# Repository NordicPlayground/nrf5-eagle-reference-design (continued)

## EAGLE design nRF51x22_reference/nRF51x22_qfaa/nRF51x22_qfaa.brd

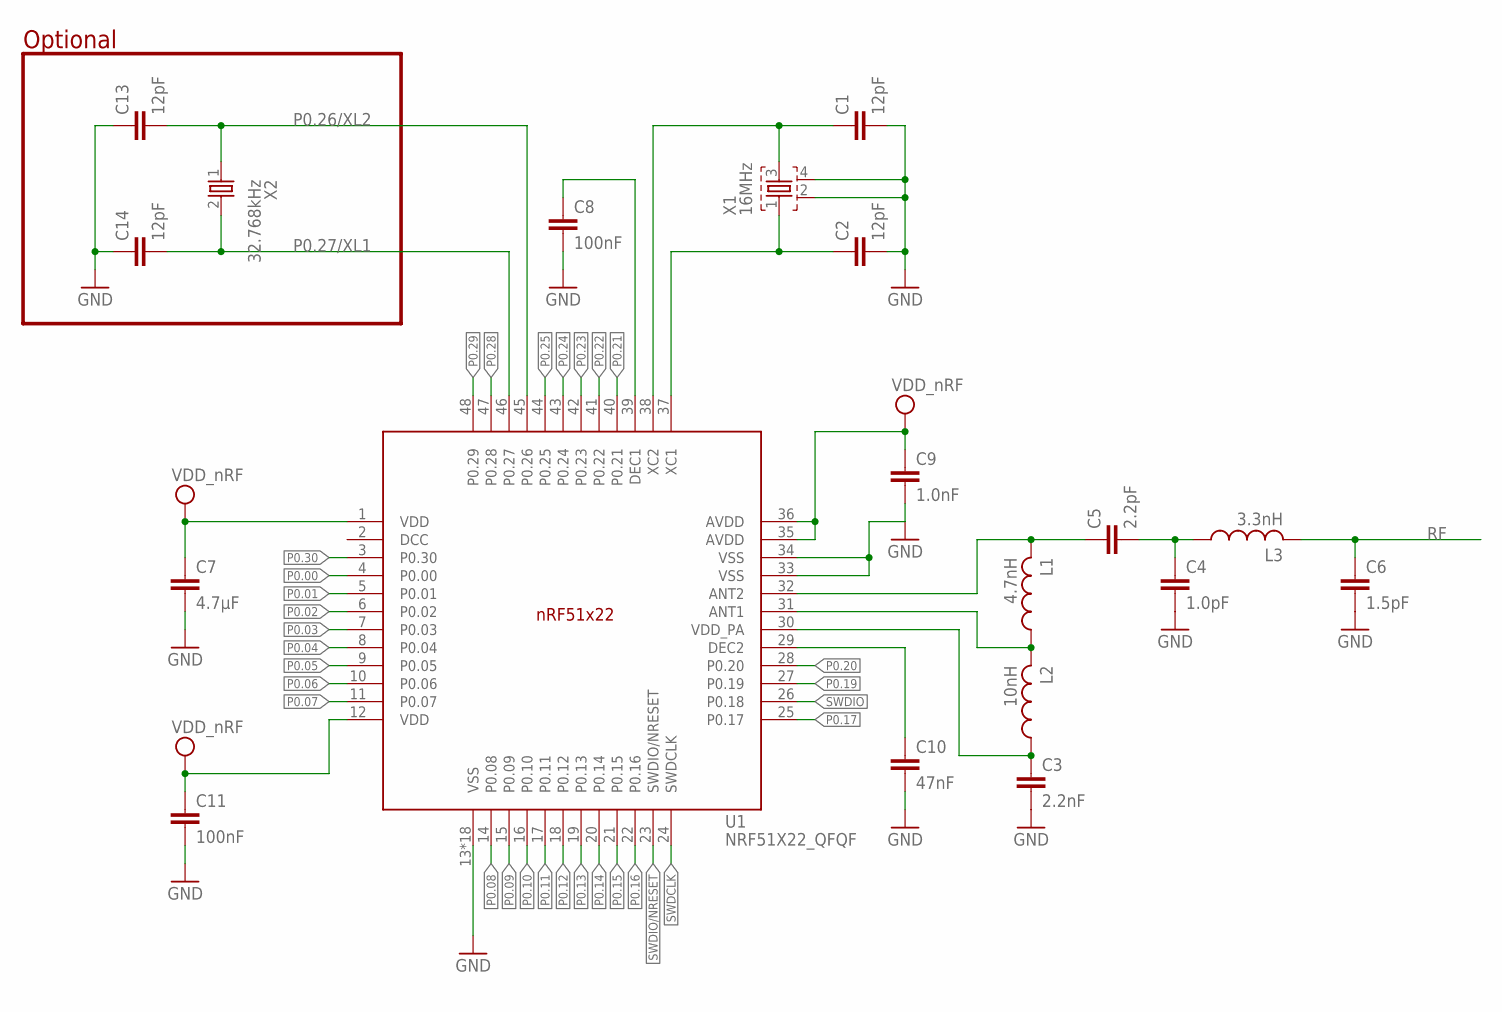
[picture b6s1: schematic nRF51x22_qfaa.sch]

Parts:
C1, C2, C13, C14: 12pF; RESC0402_N
C3: 2.2nF; RESC0402_N
C4: 1.0pF; RESC0402_N
C5: 2.2pF; RESC0402_N
C6: 1.5pF; RESC0402_N
C7: 4.7µF; RESC0603_N
C8, C11: 100nF; RESC0402_N
C9: 1.0nF; RESC0402_N
C10: 47nF; RESC0402_N
L1: 4.7nH; RESC0402_N
L2: 10nH; RESC0402_N
L3: 3.3nH; RESC0402_N
U1: NRF51X22_QFQF; QFN40P600X600X90-48_N
X1: 16MHz; BT-XTAL_2016_N
X2: 32.768kHz; XTAL_3215_N

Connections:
DCC: U1.2 (DCC)
GND: C1.2, C2.2, C3.2, C4.2, C6.2, C7.2, C8.2, C9.2, C10.2, C11.2, C13.1, C14.1, U1.13 (VSS), U1.33 (VSS), U1.34 (VSS), U1.PAD (VSS), U1.PAD@VIA01 (VSS), U1.PAD@VIA02 (VSS), U1.PAD@VIA03 (VSS), U1.PAD@VIA04 (VSS), U1.PAD@VIA05 (VSS), U1.PAD@VIA06 (VSS), U1.PAD@VIA07 (VSS), U1.PAD@VIA08 (VSS), U1.PAD@VIA09 (VSS), U1.PAD@VIA10 (VSS), U1.PAD@VIA11 (VSS), U1.PAD@VIA12 (VSS), U1.PAD@VIA13 (VSS), U1.PAD@VIA14 (VSS), U1.PAD@VIA15 (VSS), U1.PAD@VIA16 (VSS), X1.2, X1.4
unnamed: L1.1, L2.2, U1.31 (ANT1)
unnamed: C1.1, U1.38 (XC2), X1.3
unnamed: C10.1, U1.29 (DEC2)
unnamed: C8.1, U1.39 (DEC1)
unnamed: C3.1, L2.1, U1.30 (VDD_PA)
unnamed: C5.1, L1.2, U1.32 (ANT2)
unnamed: C4.1, C5.2, L3.1
P0.00: U1.4 (P0.00)
P0.01: U1.5 (P0.01)
P0.02: U1.6 (P0.02)
P0.03: U1.7 (P0.03)
P0.04: U1.8 (P0.04)
P0.05: U1.9 (P0.05)
P0.06: U1.10 (P0.06)
P0.07: U1.11 (P0.07)
P0.08: U1.14 (P0.08)
P0.09: U1.15 (P0.09)
P0.10: U1.16 (P0.10)
P0.11: U1.17 (P0.11)
P0.12: U1.18 (P0.12)
P0.13: U1.19 (P0.13)
P0.14: U1.20 (P0.14)
P0.15: U1.21 (P0.15)
P0.16: U1.22 (P0.16)
P0.17: U1.25 (P0.17)
P0.19: U1.27 (P0.19)
P0.20: U1.28 (P0.20)
P0.21: U1.40 (P0.21)
P0.22: U1.41 (P0.22)
P0.23: U1.42 (P0.23)
P0.24: U1.43 (P0.24)
P0.25: U1.44 (P0.25)
P0.26/XL2: C13.2, U1.45 (P0.26), X2.1
P0.27/XL1: C14.2, U1.46 (P0.27), X2.2
P0.28: U1.47 (P0.28)
P0.29: U1.48 (P0.29)
P0.30: U1.3 (P0.30)
RF: C6.1, L3.2
SWDCLK: U1.24 (SWDCLK)
SWDIO: U1.26 (P0.18)
SWDIO/NRESET: U1.23 (SWDIO/NRESET)
VDD_NRF: C7.1, C9.1, C11.1, U1.1 (VDD), U1.12 (VDD), U1.35 (AVDD), U1.36 (AVDD)
X1: C2.1, U1.37 (XC1), X1.1

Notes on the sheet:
Optional

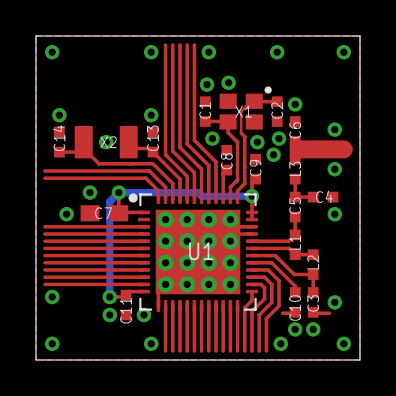
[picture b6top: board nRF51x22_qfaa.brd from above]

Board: 2 copper layers, 18.0 x 18.0 mm, 19 parts (0 on the bottom side), 13 nets.

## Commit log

2016-06-15 Finished? footprint and symbol for nRF5, QFN. Done som experimenting on board layouts
2016-06-15 Changd layer of silkscreen
2016-06-15 Fixed chip components(resistors) Moved physical outline to tDocu layer
2016-06-15 Added description on nRF chips
2016-06-16 Connected BGA package and symbols
2016-06-16 Added antennas, added passive components
2016-06-16 Fixed paste, and soldermask layers in antennas
2016-06-16 Fixed silkscreen on meander antenna
2016-06-17 Added SOT223 and TLV1117
2016-06-17 Added courtyard to XTAL2016
2016-06-17 Added courtyard to XTAL3215
2016-06-17 Renamed pads on XTAL3215 (removed $)
2016-06-17 Renamed pads on XTAL2016 (removed $)
2016-06-17 Moved resistor value inside resistor
2016-06-17 Added MM8130-2600
2016-06-17 Added NFC and SWO to symbol for nrf52
2016-06-20 Added microusb
2016-06-20 Routed gpio
2016-06-21 Added switches
2016-06-21 Positioned buttons, positioned powersupply
2016-06-21 Removed all non-library files (not ready for publishing)
2016-06-21 Split library into two, nRF (core parts), and misc
2016-06-21 Added brief readme
2016-06-21 punctuation
2016-06-21 Added licence (TBC?)
2016-06-21 Readded nRF52832_MCU_Board
2016-06-21 Fixed library links
2016-06-21 Added LED
2016-06-21 Fixed polarity on CR1632
2016-06-21 Done some layout
2016-06-21 Squezed in nfc antenna connector
2016-06-21 Connected all signals in layout
2016-06-21 Copyed layout from nano to arduino
2016-06-22 Copied altium reference designs
2016-06-22 Added more vias
2016-06-22 Added NFC antenna
2016-06-22 Looked at arduino layout
2016-06-22 Started Getting-started.md
2016-06-23 Copied reference layout from altium
2016-06-23 Removed old files
2016-06-23 Cleanup in layout
2016-06-23 Added two connections to CR1632
2016-06-23 Added some vias
2016-06-23 Generated pdfs of reference designs
2016-06-23 Cleaned up schematic
2016-06-23 Written some more on getting started
2016-06-23 Looked into different layout
2016-06-27 Written more detailed
2016-06-28 Restructured MCU_Board
2016-06-28 Regenerated pdfs with polygons pured
2016-06-28 Rearranged
2016-06-28 png for getting started
2016-06-28 resized
2016-06-28 Removed dummy text
2016-06-28 Copy pasted from getting started to readme
2016-06-28 Fixed comments from David Garcia Polo
2016-06-30 Added silk, name and value to FPC_05P-RA-SMD
2016-06-30 Aded name and value to HDRV127P5X2-10_N
2016-06-30 Modified silk, Added name and value to MM8130-2600
2016-06-30 Added silk to PANASONIC_EVQPT5A15
2016-06-30 Added silk, name and value to USB-MICRO-B-RA-SMD-PIP
2016-06-30 Added more silk to BT-XTAL_2016_N
2016-06-30 Added silk to XTAL_3215_N
2016-06-30 Updated silk on some components, fixed via clearance at NFC and decoupling, fixed clearance at batt, routed XL1 and XL2, tented vias
2016-06-30 Added name and value to SOT220P700-4_N
2016-06-30 Fixed wrong layer of value on MM8130-2600
2016-06-30 Done some work in silk
2016-06-30 Modifications from review
2016-07-04 Added more vias, fixed error in silkscreen at J1
2016-07-04 Added name to headers in library, named headers properly
2016-07-04 Ran DRC, approved errors
2016-07-08 Moved copper plane away from antenna connection point
2016-07-11 Generated gerber
2016-08-01 Added nRF52 WLCSP
2016-09-06 Issue #2: Fixed value of C7 from 100nF to 100pF
2016-12-01 Issue #3: Fixed wrong connections on P0.21/RESET - 6 and P0.18/SWO - 10
2017-01-24 Added nrf52840
2017-01-24 Updated bga pad size according to IPC-7351
2017-07-13 Added nRF52810
2017-08-17 Added description
2017-08-17 Fixed description for CIAA_WLCSP_C62_N.pac
2017-11-01 fix(project): change GitHub organization to NordicPlayground
2018-04-06 Mislabeled nRF52840 DEC6 Pin, closes #5
2018-05-02 Small label/designator update, fixes #6
2018-05-02 Same fixes as in qfaa_dcdc
2018-08-23 Removed 'nRF52832_MCU-board'
2018-08-23 Resized nRF52810 schematic symbol to same size as nRF52832, also renamed to the proper Packet variant name
2018-08-23 Added nRF52810_qfaa reference layout (copied from nRF52832_qfaa, pin compatible)
2018-08-23 Eagle did not save properly
2018-08-24 Added nRF52810_qcaa reference
2018-08-24 Added packaging codes in names
2018-08-28 Started nRF52840 reference layout
2018-12-14 Updated nRF52840 pad sizes to match altium library
2019-04-09 Added clarification that only the Altium reference designs are official
2019-04-09 Generated pdfs
2020-02-15 Added nRF52811 CAAA WLCSP
2022-03-17 Fix 52840-QI name, add part for 52840-QF
2022-03-22 Revert changed unit
2022-03-22 Fixed symbol and connections removed from NRF52840_QI
2022-03-22 Fixed odd shape of symbol
2022-03-22 Reapplied unit fix
